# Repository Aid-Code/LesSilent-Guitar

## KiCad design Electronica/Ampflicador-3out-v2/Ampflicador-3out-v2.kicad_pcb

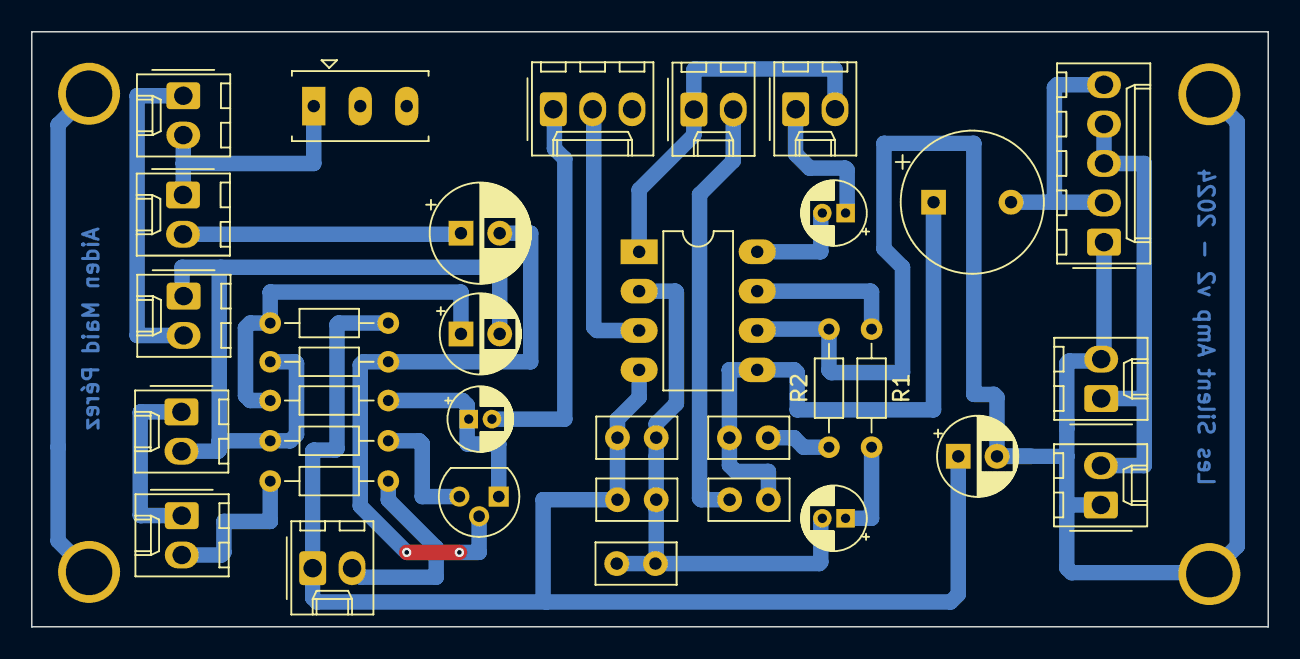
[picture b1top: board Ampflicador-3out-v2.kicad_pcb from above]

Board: 2 copper layers, 79.8 x 38.4 mm, 34 parts (0 on the bottom side), 22 nets.

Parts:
BT1: Power Input; Molex_KK-254_AE-6410-02A_1x02_P2.54mm_Vertical
C1, C3, C7: 0,1µF; C_Disc_D5.0mm_W2.5mm_P2.50mm
C2, C11: 100µF; CP_Radial_D5.0mm_P2.50mm
C4: 470pF; C_Disc_D5.0mm_W2.5mm_P2.50mm
C5, C6: 10µF; CP_Radial_D4.0mm_P1.50mm
C8: 33nF; C_Disc_D5.0mm_W2.5mm_P2.50mm
C9: 1000µF; CP_Radial_Tantal_D9.0mm_P5.00mm
C10: 0,1µF; CP_Radial_D6.3mm_P2.50mm
C12: 4,7µF; CP_Radial_D4.0mm_P1.50mm
D1: LED; Molex_KK-254_AE-6410-02A_1x02_P2.54mm_Vertical
J1: Jack 6.5; Molex_KK-254_AE-6410-02A_1x02_P2.54mm_Vertical
LS1: Speaker; Molex_KK-254_AE-6410-02A_1x02_P2.54mm_Vertical
Output-Jack-3.5: AudioJack2_Ground_Switch; Molex_KK-254_AE-6410-05A_1x05_P2.54mm_Vertical
P1: Piezo 1; Molex_KK-254_AE-6410-02A_1x02_P2.54mm_Vertical
P2, P3: Piezo 2; Molex_KK-254_AE-6410-02A_1x02_P2.54mm_Vertical
Q1: MPF102; TO-92
R1: 10KΩ; R_Axial_DIN0204_L3.6mm_D1.6mm_P7.62mm_Horizontal
R2, R6: 10Ω; R_Axial_DIN0204_L3.6mm_D1.6mm_P7.62mm_Horizontal
R3: 10MΩ; R_Axial_DIN0204_L3.6mm_D1.6mm_P7.62mm_Horizontal
R4: 470Ω; R_Axial_DIN0204_L3.6mm_D1.6mm_P7.62mm_Horizontal
R5: 1,2kΩ; R_Axial_DIN0204_L3.6mm_D1.6mm_P7.62mm_Horizontal
R7: 430Ω; R_Axial_DIN0204_L3.6mm_D1.6mm_P7.62mm_Horizontal
RV1: Volume; Molex_KK-254_AE-6410-03A_1x03_P2.54mm_Vertical
RV2: Gain; Molex_KK-254_AE-6410-02A_1x02_P2.54mm_Vertical
RV3: Bass; Molex_KK-254_AE-6410-02A_1x02_P2.54mm_Vertical
SW1: SW_DPST_x2; Molex_KK-254_AE-6410-02A_1x02_P2.54mm_Vertical
SW2: SW_DPST_x2; SW_Slide_SPDT_Straight_CK_OS102011MS2Q
U1: LM386; DIP-8_W7.62mm_LongPads

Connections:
GND: BT1.2 (-), C1.2, C2.2, C3.1, C4.1, C4.2, C5.2, C11.2, LS1.2, P3.1, R2.2, R3.2, R4.2, RV1.3, SW2.2 (B), U1.2 (-), U1.6 (V+)
unnamed: BT1.1 (+), SW1.1 (A)
unnamed: C5.1, R1.2
unnamed: C6.1, RV2.1
unnamed: C6.2, U1.8 (GAIN)
unnamed: C7.1, C8.2, C9.1, U1.5
unnamed: C7.2, R2.1
unnamed: C8.1, RV3.2
unnamed: C10.1, P1.2
unnamed: C11.1, R5.1, R6.1
unnamed: C12.2, RV1.1
unnamed: D1.2 (A), R7.2
unnamed: C1.1, C2.1, C3.2, D1.1 (K), R6.2, U1.4 (GND)
unnamed: P2.1, P3.2
unnamed: C12.1, Q1.1 (D), R5.2
unnamed: C10.2, Q1.2 (G), R3.1
unnamed: Q1.3 (S), R4.1
unnamed: RV2.2, RV3.1, U1.1 (GAIN)
unnamed: R7.1, SW1.2 (B)
unnamed: P1.1, P2.2, SW2.1 (A)
unnamed: RV1.2, U1.3 (+)
unnamed: R1.1, U1.7 (BYPASS)

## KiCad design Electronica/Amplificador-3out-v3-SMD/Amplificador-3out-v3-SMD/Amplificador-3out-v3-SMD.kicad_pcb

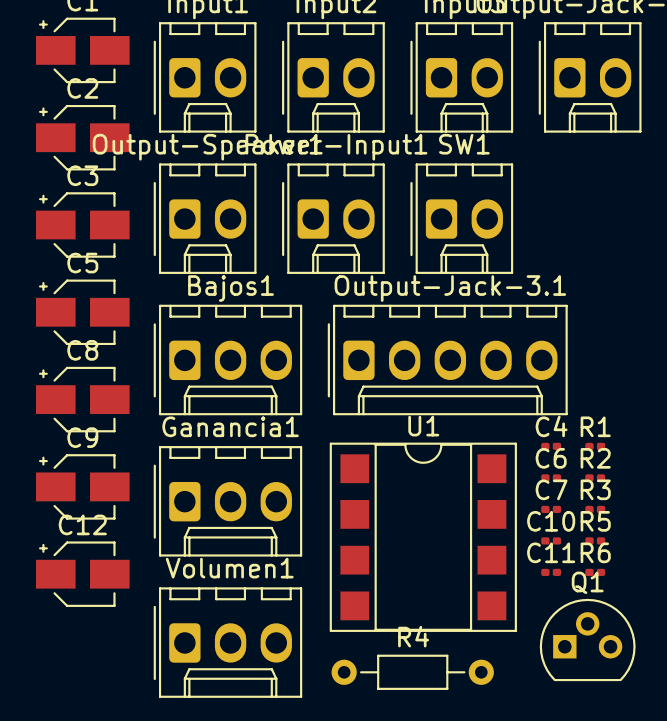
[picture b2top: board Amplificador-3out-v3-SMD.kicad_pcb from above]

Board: 2 copper layers, 31 parts (0 on the bottom side), 18 nets, no tracks yet.

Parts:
Bajos1: 10KΩ; Molex_KK-254_AE-6410-03A_1x03_P2.54mm_Vertical
C1: 0,1µF; CP_Elec_3x5.3
C2, C5: 100µF; CP_Elec_3x5.3
C3: 4,7µF; CP_Elec_3x5.3
C4, C6, C10: 0,1µF; C_0201_0603Metric
C7: 470pF; C_0201_0603Metric
C8, C9: 10µF; CP_Elec_3x5.3
C11: 33nF; C_0201_0603Metric
C12: 1000µF; CP_Elec_3x5.3
Ganancia1: 10KΩ; Molex_KK-254_AE-6410-03A_1x03_P2.54mm_Vertical
Input1, Input2, Input3: Screw_Terminal_01x02; Molex_KK-254_AE-6410-02A_1x02_P2.54mm_Vertical
Output-Jack-3.1: AudioJack2_Ground_Switch; Molex_KK-254_AE-6410-05A_1x05_P2.54mm_Vertical
Output-Jack-6.1: Screw_Terminal_01x02; Molex_KK-254_AE-6410-02A_1x02_P2.54mm_Vertical
Output-Speaker1: Screw_Terminal_01x02; Molex_KK-254_AE-6410-02A_1x02_P2.54mm_Vertical
Power-Input1: Screw_Terminal_01x02; Molex_KK-254_AE-6410-02A_1x02_P2.54mm_Vertical
Q1: MPF102; TO-92
R1: 10MΩ; R_0201_0603Metric
R2: 1,2kΩ; R_0201_0603Metric
R3: 470Ω; R_0201_0603Metric
R4: 10Ω; R_Axial_DIN0204_L3.6mm_D1.6mm_P7.62mm_Horizontal
R5: 10KΩ; R_0201_0603Metric
R6: 10Ω; R_0201_0603Metric
SW1: SW_DPST_x2; Molex_KK-254_AE-6410-02A_1x02_P2.54mm_Vertical
U1: LM386; DIP-8_W7.62mm_SMDSocket_SmallPads
Volumen1: 10KΩ; Molex_KK-254_AE-6410-03A_1x03_P2.54mm_Vertical

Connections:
GND: C2.2, C4.2, C5.2, C6.1, C7.1, C7.2, C8.2, Input1.1, Input2.1, Input3.1, Output-Jack-6.1.2, Output-Speaker1.2, Power-Input1.1, R1.2, R3.2, R6.2, U1.2 (-), U1.6 (V+), Volumen1.3
unnamed: Bajos1.2, C11.1
unnamed: Bajos1.3, Ganancia1.2, U1.1 (GAIN)
unnamed: C2.1, R2.1, R4.1
unnamed: C3.2, Volumen1.1
unnamed: C8.1, R5.2
unnamed: C9.1, Ganancia1.1
unnamed: C9.2, U1.8 (GAIN)
unnamed: C10.1, C11.2, C12.1, U1.5
unnamed: C10.2, R6.1
unnamed: C1.1, Input1.2, Input2.2, Input3.2
unnamed: Power-Input1.2, SW1.1 (A)
unnamed: C3.1, Q1.1 (D), R2.2
unnamed: C1.2, Q1.2 (G), R1.1
unnamed: Q1.3 (S), R3.1
unnamed: C4.1, C5.1, C6.2, R4.2, SW1.2 (B), U1.4 (GND)
unnamed: U1.3 (+), Volumen1.2
unnamed: R5.1, U1.7 (BYPASS)

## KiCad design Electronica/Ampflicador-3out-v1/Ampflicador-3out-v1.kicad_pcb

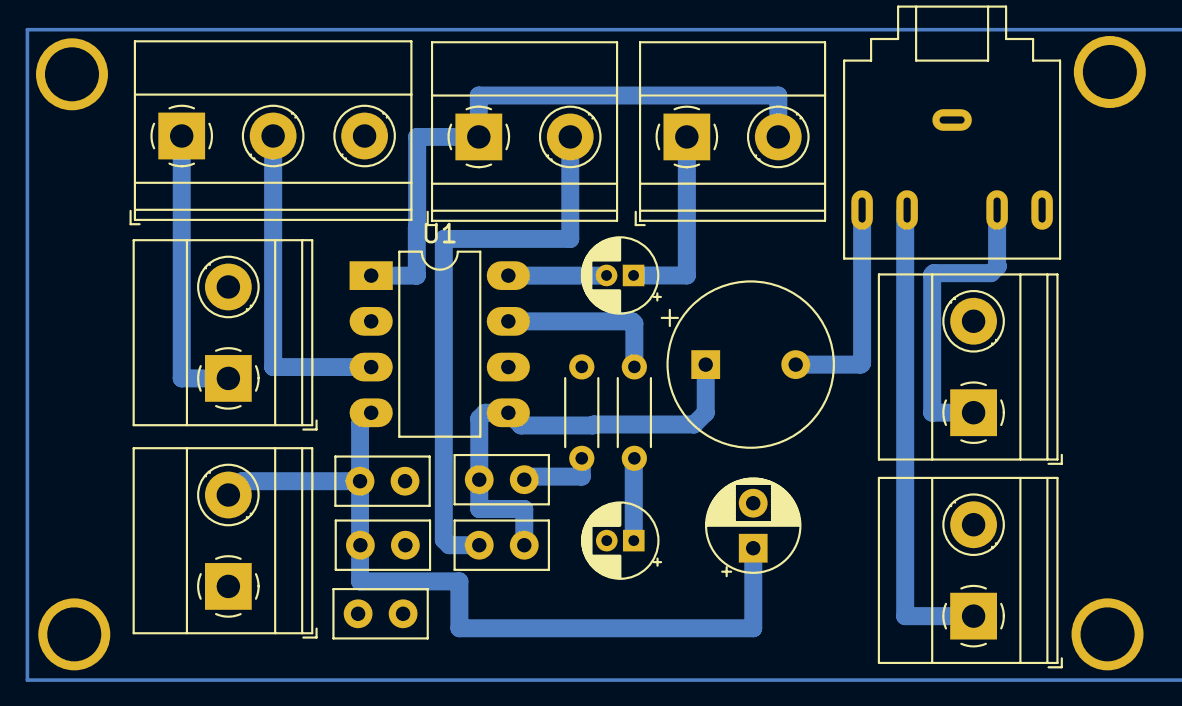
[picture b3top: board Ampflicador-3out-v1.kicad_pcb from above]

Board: 2 copper layers, 20 parts (0 on the bottom side), 15 nets.

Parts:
Bass1: Screw_Terminal_01x02; TerminalBlock_Phoenix_MKDS-1,5-2-5.08_1x02_P5.08mm_Horizont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
C1, C3, C5: 0,1µF; C_Disc_D5.0mm_W2.5mm_P2.50mm
C2: 470pF; C_Disc_D5.0mm_W2.5mm_P2.50mm
C4: 33nF; C_Disc_D5.0mm_W2.5mm_P2.50mm
C6: 100µF; CP_Radial_D5.0mm_P2.50mm
C7, C8: 10µF; CP_Radial_D4.0mm_P1.50mm
C9: 1000µF; CP_Radial_Tantal_D9.0mm_P5.00mm
Gain1: Screw_Terminal_01x02; TerminalBlock_Phoenix_MKDS-1,5-2-5.08_1x02_P5.08mm_Horizont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
Output-Jack-3.5: AudioJack2_Ground_Switch; Jack_3.5mm_CUI_SJ1-3525N_Horizontal
Output-Jack-6.5: Screw_Terminal_01x02; TerminalBlock_Phoenix_MKDS-1,5-2-5.08_1x02_P5.08mm_Horizont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
Output-Speaker1: Screw_Terminal_01x02; TerminalBlock_Phoenix_MKDS-1,5-2-5.08_1x02_P5.08mm_Horizont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
Piezo-Input1: Screw_Terminal_01x02; TerminalBlock_Phoenix_MKDS-1,5-2-5.08_1x02_P5.08mm_Horizont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
Power-Input1: Screw_Terminal_01x02; TerminalBlock_Phoenix_MKDS-1,5-2-5.08_1x02_P5.08mm_Horizont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
R1: 10KΩ; R_Axial_DIN0204_L3.6mm_D1.6mm_P5.08mm_Horizontal
R2: 10Ω; R_Axial_DIN0204_L3.6mm_D1.6mm_P5.08mm_Horizontal
U1: LM386; DIP-8_W7.62mm_LongPads
Vol1: Screw_Terminal_01x03; TerminalBlock_Phoenix_MKDS-1,5-3-5.08_1x03_P5.08mm_Horizont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

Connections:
GND: C1.2, C2.1, C2.2, C3.1, C6.2, C7.2, Output-Jack-3.5.S, Output-Jack-6.5.2, Output-Speaker1.2, Piezo-Input1.2, Power-Input1.1, R2.2, U1.2 (-), U1.6 (V+), Vol1.3
unnamed: Bass1.1, Gain1.2, U1.1 (GAIN)
unnamed: Bass1.2, C4.1
unnamed: C4.2, C5.1, C9.1, U1.5
unnamed: C5.2, R2.1
unnamed: C7.1, R1.2
unnamed: C8.2, U1.8 (GAIN)
unnamed: C9.2, Output-Jack-3.5.T
unnamed: C8.1, Gain1.1
unnamed: Output-Jack-3.5.RN, Output-Jack-6.5.1
unnamed: Output-Jack-3.5.TN, Output-Speaker1.1
unnamed: Piezo-Input1.1, Vol1.1
unnamed: C1.1, C3.2, C6.1, Power-Input1.2, U1.4 (GND)
unnamed: U1.3 (+), Vol1.2
unnamed: R1.1, U1.7 (BYPASS)

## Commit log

2024-04-04 Datasheet LM386
2024-04-29 PCB Amp V1 casi terminada
2024-05-01 Amp v1 sin plano de masa
2024-05-02 Amp V1
    Plano de masa
    Cambiar pads de los cap. de 10microF
2024-05-03 Amp V2 - No terminado
    Buffer para piezo
    No esta terminado
2024-05-14 Amp v2
2024-05-15 Amp v2 terminada - sin molex
2024-05-15 Amp v2 sin terminar - con molex
2024-05-15 PCB Amp v2 terminada - Molex
    Plano de masa
    Conectores Molex
    3 piezos
    Suma de señales de entrada
2024-05-16 Amp v2 - Molex y pistas 45°
2024-05-16 Amp v2 terminada - Pistas 45°
2024-06-03 Amp v2 sin plano masa
2024-06-04 Amp v2 sin acordate
2024-06-04 Amp v2 sin termianr
2024-06-06 Amp creo que para imprimir
2024-06-10 Amp V2 con Led
2024-06-11 Modelos en STEP Componentes
2024-06-11 Archivo STEP Amp ultima version
